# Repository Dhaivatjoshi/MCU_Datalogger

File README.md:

---

## **MCU Data Logger – PCB Design with KiCad**  

### **Project Overview**  
This project is an **MCU-based Data Logger** designed to improve my skills in PCB design and embedded systems. The PCB was developed using **KiCad**, incorporating key components for reliable data logging and real-time tracking. This project helped me refine my understanding of component placement, routing, and communication protocols.  

### **Key Features**  
✅ **2-Layer PCB Design** – Created and optimized using KiCad.  
✅ **Microcontroller** – ATmega328P-AU for processing and control.  
✅ **Non-Volatile Storage** – 24LC1025 EEPROM for data logging.  
✅ **Real-Time Clock** – DS1337 RTC for accurate timekeeping.  
✅ **Communication Interfaces** – Supports UART, SPI, and I2C for flexibility.  
✅ **GPIOs for Expansion** – Designed with future scalability in mind.  
✅ **3D PCB Visualization** – Front, back, and combined views for better insights.  

---

## **Project Flow**  

1️⃣ **Microcontroller (ATmega328P-AU)**  
   - Handles all system operations and manages communication.  
   - Reads and writes data to EEPROM for storage.  
   
2️⃣ **RTC Module (DS1337)**  
   - Provides accurate timestamps for logged data.  
   - Communicates via I2C with the MCU.  
   
3️⃣ **EEPROM Storage (24LC1025)**  
   - Stores logged data persistently.  
   - Connected over I2C for data transfer.  

4️⃣ **Communication Interfaces**  
   - **UART**: Serial communication for debugging/logging.  
   - **SPI & I2C**: Expandability for additional peripherals.  

5️⃣ **Power Management & PCB Layout**  
   - Designed for stable operation with proper power routing.  
   - Optimized signal paths to reduce interference and improve reliability.  

---

## **PCB Design & Visualizations**  

### **1️⃣ Front Copper Layer**  

### **2️⃣ Back Copper Layer**  

### **3️⃣ Combined (Both Layers)**  

### **4️⃣ 3D Model (Front & Back)**  

### **5️⃣ 3D Model with CAD Casing (Designed in Creo)**  

---

## **Download & Build**  
📥 You can download the complete project files, including KiCad PCB designs, and schematics from my **GitHub repository**  

---

## **Feedback & Suggestions**  
I'm constantly learning and improving my PCB design skills. If you're experienced with KiCad or embedded systems, I'd love to hear your thoughts! Feel free to open an **issue** or drop a **comment**. 🚀  

---

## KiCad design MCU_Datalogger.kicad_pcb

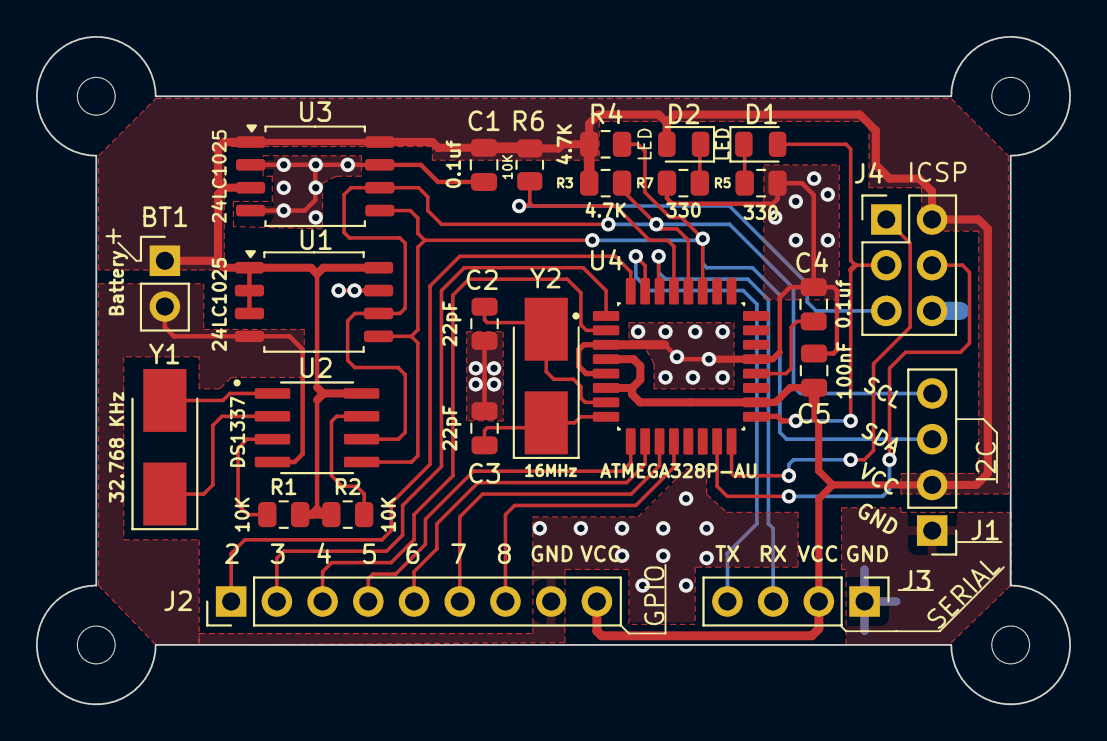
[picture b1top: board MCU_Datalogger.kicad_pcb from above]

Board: 2 copper layers, 57.4 x 37.1 mm, 29 parts (0 on the bottom side), 26 nets.

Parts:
BT1: Battery; PinHeader_1x02_P2.54mm_Vertical
C1, C4: 0.1uf; C_0805_2012Metric
C2, C3: 22pF; C_0805_2012Metric
C5: 100nF; C_0805_2012Metric
D1, D2: LED; LED_0805_2012Metric
H1, H2, H3, H4: MountingHole; MountingHole_2.1mm
J1, J3: Conn_01x04_Pin; PinHeader_1x04_P2.54mm_Vertical
J2: Conn_01x09_Pin; PinHeader_1x09_P2.54mm_Vertical
J4: Conn_02x03_Odd_Even; PinHeader_2x03_P2.54mm_Vertical
R1, R2, R6: 10K; R_0805_2012Metric
R3, R4: 4.7K; R_0805_2012Metric
R5, R7: 330; R_0805_2012Metric
U1, U3: 24LC1025; SOIC-8_5.3x5.3mm_P1.27mm
U2: DS1337; SOIC127P600X175-8N
U4: ATMEGA328P-AU; QFP80P900X900X120-32N
Y1: 32.768 KHz; Crystal_SMD_5032-2Pin_5.0x3.2mm_HandSoldering
Y2: 16MHz; Crystal_SMD_5032-2Pin_5.0x3.2mm_HandSoldering

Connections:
/D2: J2.1, U4.32 (PD2)
/D3: J2.2, U4.1 (PD3)
/D4: J2.3, U4.2 (PD4)
/D5: J2.4, U4.9 (PD5)
/D6: J2.5, U4.10 (PD6)
/D7: J2.6, U4.11 (PD7)
/D8: J2.7, U4.12 (PB0)
/MISO: J4.1, U4.16 (PB4)
/MOSI: J4.4, U4.15 (PB3)
/RESET: J4.5, R6.2, U4.29 (PC6/~RESET)
/RX: J3.3, U4.30 (PD0)
/SCK: D1.2 (A), J4.3, U4.17 (PB5)
/SCL: J1.4, R3.2, U1.6 (SCL), U2.6 (SCL), U3.6 (SCL), U4.28 (PC5)
/SDA: J1.3, R4.2, U1.5 (SDA), U2.5 (SDA), U3.5 (SDA), U4.27 (PC4)
/TX: J3.4, U4.31 (PD1)
/Vcc: BT1.1 (+), C1.1, C5.1, D2.2 (A), J1.2, J2.9, J3.2, J4.2, R1.1, R2.1, R3.1, R4.1, R6.1, U1.1 (A0), U1.2 (A1), U1.3 (A2), U1.8 (VCC), U2.8 (VCC), U3.1 (A0), U3.3 (A2), U3.8 (VCC), U4.4 (VCC), U4.6 (VCC), U4.18 (AVCC)
GND: BT1.2 (-), C1.2, C2.1, C3.1, C4.1, C5.2, J1.1, J2.8, J3.1, J4.6, R5.1, R7.2, U1.4 (GND), U1.7 (WP), U2.4 (GND), U3.2 (A1), U3.4 (GND), U3.7 (WP), U4.3 (GND), U4.5 (GND), U4.21 (GND)
unnamed: D1.1 (K), R5.2
unnamed: D2.1 (K), R7.1
unnamed: R2.2, U2.7 (SQW/~INT)
unnamed: U2.1 (X1), Y1.2
unnamed: U2.2 (X2), Y1.1
unnamed: R1.2, U2.3 (~INTA)
unnamed: C4.2, U4.20 (AREF)
unnamed: C2.2, U4.7 (PB6), Y2.2
unnamed: C3.2, U4.8 (PB7), Y2.1

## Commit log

2025-03-16 init
2025-03-16 Sch_setup_complete
2025-03-17 add all component
2025-03-17 Create sym-lib-table
2025-03-17 change the location of symbols(arrange) and annotate
2025-03-17 update symbol value
2025-03-17 completed symbol-footprint assignment
2025-03-17 Completed Sch wiring
2025-03-17 Complete wiring in second Sch
2025-03-17 Allocated GND and VCC to net class
2025-03-17 Completed Comment
2025-03-20 Setup Pcbnew
2025-03-20 Completed placement of footprint
2025-03-30 Routing, GND Plane, Rework VCC Line and slick Screen complete
2025-03-31 final 2 layer Layout
2025-03-31 add image folder - Output PCB schematic and Layout with 3d model
2025-04-08 Add CAD 3d Model
